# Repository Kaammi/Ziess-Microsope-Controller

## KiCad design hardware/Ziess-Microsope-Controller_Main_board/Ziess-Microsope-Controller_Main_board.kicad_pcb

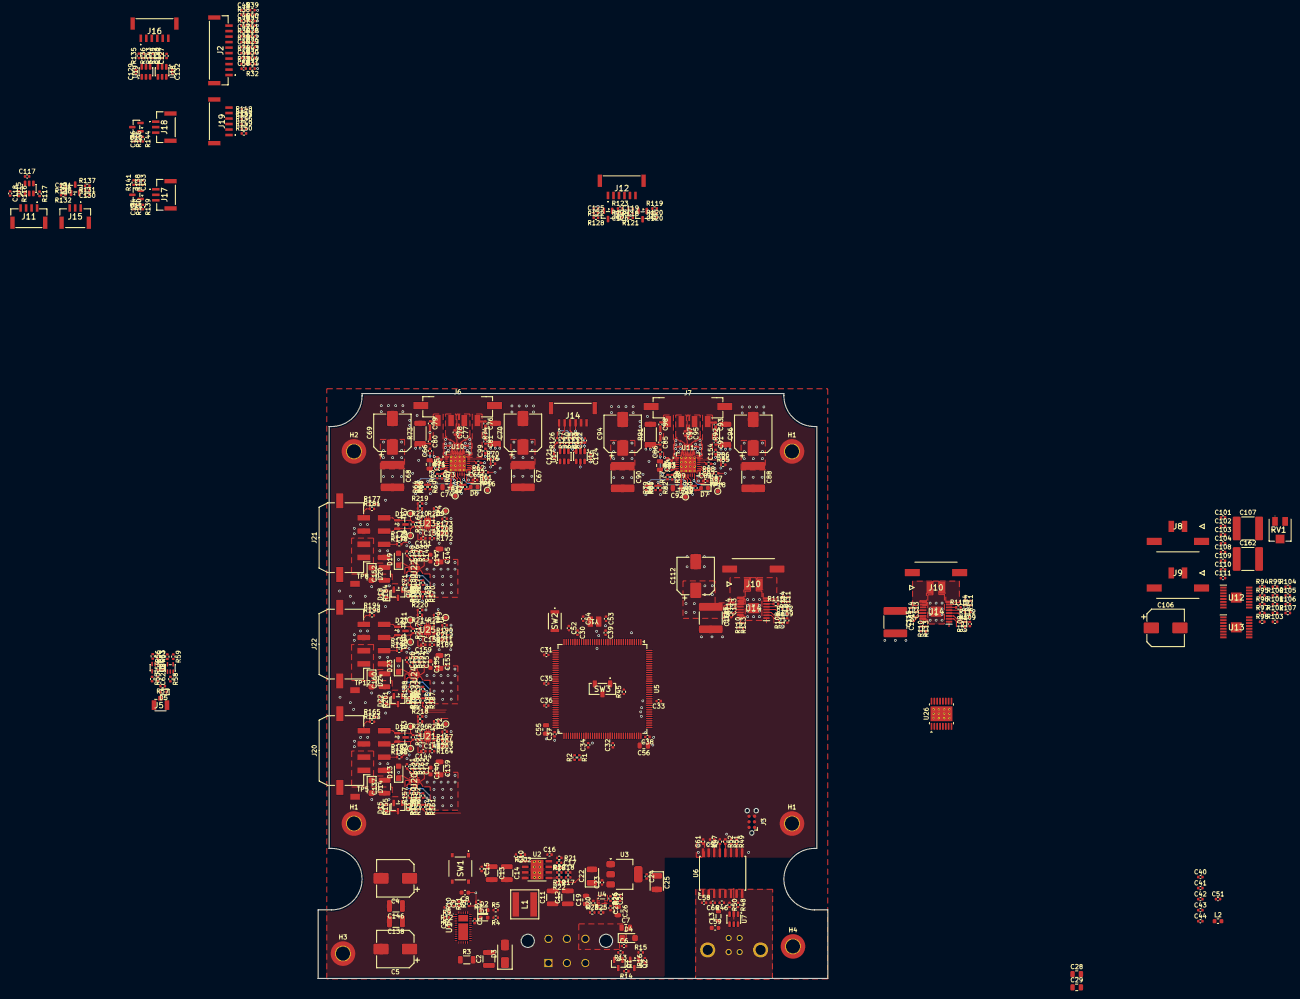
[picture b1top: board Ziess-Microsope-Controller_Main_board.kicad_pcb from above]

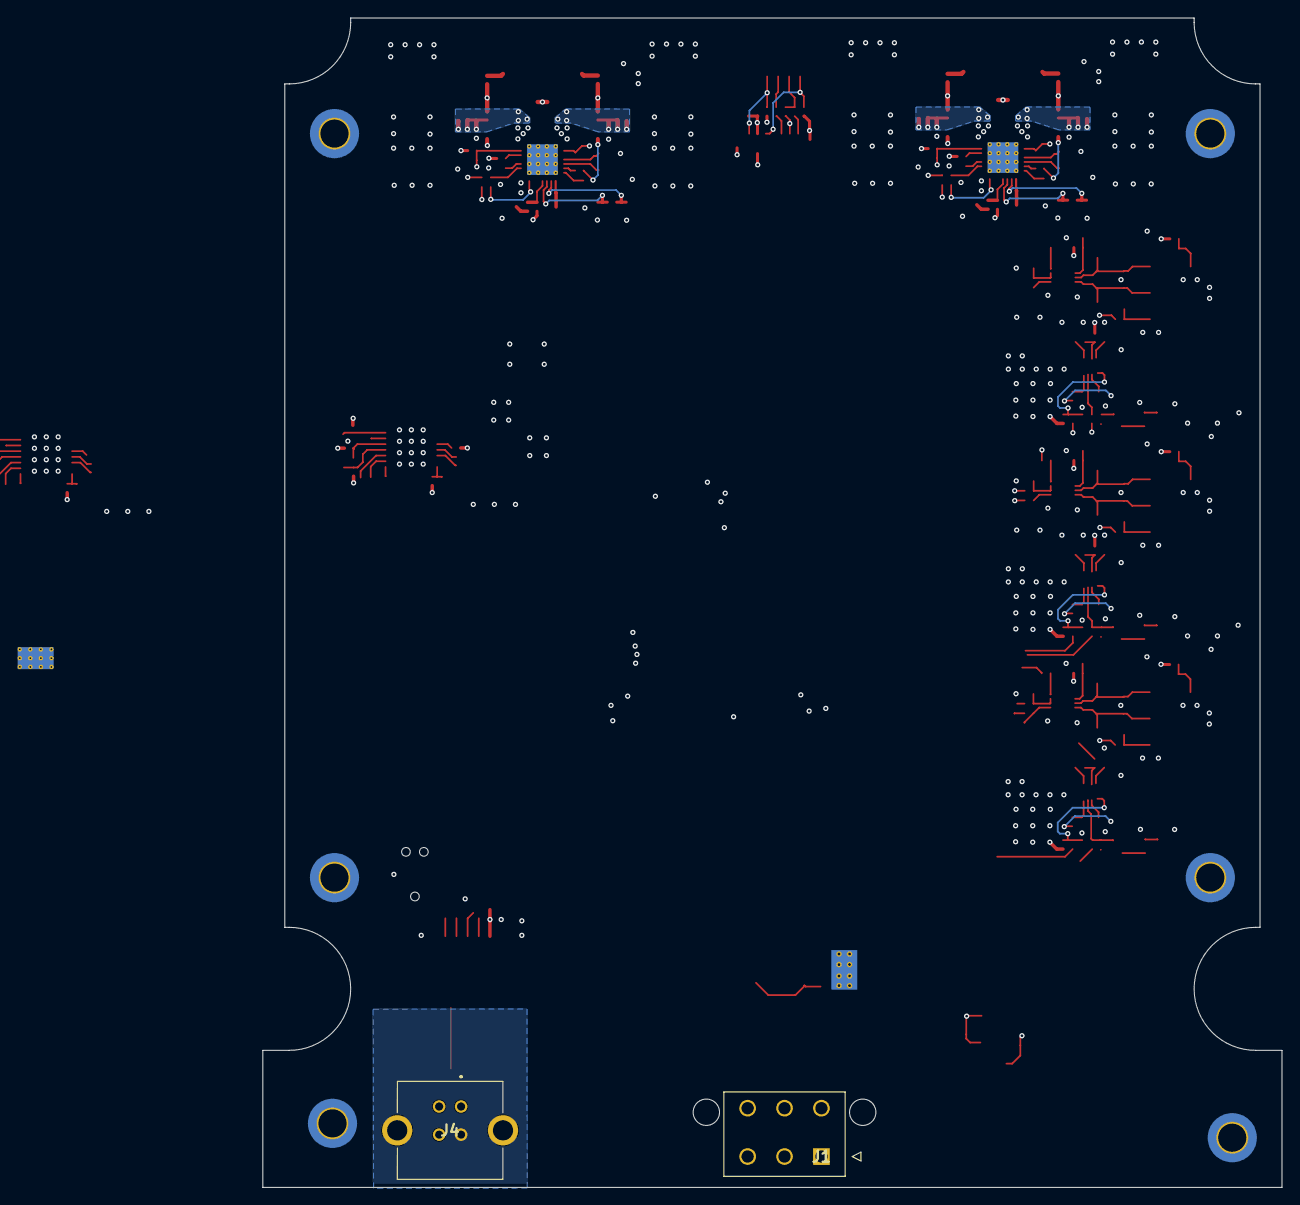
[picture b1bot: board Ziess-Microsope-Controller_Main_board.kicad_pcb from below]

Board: 4 copper layers, 116.0 x 133.1 mm, 498 parts (2 on the bottom side), 244 nets.

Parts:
C1, C3, C6, C9, C10, C20, C21, C23, C24, C27, C30, C31, C32, C33, C34, C35, C36, C37, C38, C39, C40, C42, C43, C44, C45, C46, C47, C48, C49, C50, C51, C52, C57, C58, C60, C61, C65, C66, C71, C72, C73, C80, C81, C82, C83, C85, C86, C87, C89, C91, C99, C101, C102, C104, C108, C109, C111, C113, C113#2, C114, C114#2, C116, C116#2, C117, C118, C119, C120, C121, C123, C124, C125, C126, C128, C129, C130, C131, C132, C133, C134, C135, C136, C143, C144, C150, C151, C154, C158, C159: 100nF; C_0402_1005Metric
C2, C13, C14: 22uF; C_1210_3225Metric
C4, C5, C106, C112: 220uF; CP_Elec_8x10
C7: 10uF; C_0805_2012Metric
C8: 1nF; C_0603_1608Metric
C11, C12: 47uF; C_1210_3225Metric
C15, C62, C63: 100nF; R_0402_1005Metric
C16: 10nF; C_0402_1005Metric
C17: 120pF; C_0402_1005Metric
C18: 12nF; C_0402_1005Metric
C19, C26, C28, C29, C74, C92: 4.7uF; C_0805_2012Metric
C22, C25: 22uF; CP_EIA-3528-21_Kemet-B
C41, C122, C127: 1uF; C_0402_1005Metric
C53, C54: 10pf; C_0402_1005Metric
C55, C56: 2.2uF; C_0805_2012Metric
C59: 2.2uF; C_0603_1608Metric
C67, C68, C88, C90, C107, C161, C161#2, C162: 10uF; C_2220_5750Metric
C69, C70, C94, C96: 100uF; CP_Elec_8x10
C75, C84: 22nF; C_0805_2012Metric
C76, C77, C78, C79, C93, C95, C97, C98: 470pF; C_0402_1005Metric
C103, C110, C115, C115#2, C141, C148, C156: 22nF; C_0402_1005Metric
C137, C152, C160: 10uF; C_1210_3225Metric
C138, C146: 47uf; C_1210_3225Metric
C139, C145, C153: 1uF; C_1206_3216Metric
C140, C147, C155: 100nF; C_0603_1608Metric
C142, C149, C157: 3.3nF; C_0402_1005Metric
D1, D6, D7: RED; LED_0603_1608Metric
D2, D15, D18, D22: GREEN; LED_0603_1608Metric
D3: SMAJ15A; D_SMA
D4: SMF5V0A; D_SMF
D5: TPD1E10B06DYARQ1; D_SOD-523
D8, D9, D10, D11, D12: SP0502BAHT; SOT-23
D13, D19, D23: PMEG4030ER; Nexperia_CFP3_SOD-123W
D14, D20, D24: SMF15A; D_SMF
D16, D17, D21: SM712_SOT23; SOT-23
H1, H1#2, H1#3, H2, H3, H4: MountingHole_Pad; MountingHole_3.2mm_M3_DIN965_Pad_TopBottom
J1: 172447-0006; 172447-YY06
J2: Conn_01x10; BM10BGHSTBT
J3: TC2030; Tag-Connect_TC2030-IDC-NL_2x03_P1.27mm_Vertical
J4: USB_B; UJ2BV1TH
J5: U.FL-R-SMT-1_10; U.FL-R-SMT-1_10_
J6, J7: 43650-0424; Molex_Micro-Fit_3.0_43650-0424_1x04-1MP_P3.00mm_Vertical
J8, J9, J10, J10#2: 43650-0224; 43650-02YY_242526
J11: BM04B-GHS-TBT; BM04BGHSTBTLFSN
J12, J14, J16, J19: BM06B-GHS-TBT; BM06BGHSTBTLFSN
J15, J17, J18: BM03B-GHS-TBT; BM03BGHSTBTLFSN
J20, J21, J22: 43045-0810; Molex_Micro-Fit_3.0_43045-0810_2x04-1MP_P3.00mm_Horizontal
L1: 15uH; SRP6060FA150M
L2: FCM1608KF-601T05; L_0603_1608Metric
L3: BLM21PG221SN1D; L_0805_2012Metric
Q1: BSS84; SOT-23
Q2, Q3, Q4, Q5: 2N7002; SOT-23
R1: 22k; R_0402_1005Metric
R2, R19, R57, R76, R85: 100k; R_0402_1005Metric
R3: 0.002; R_1206_3216Metric
R4, R5, R8, R9, R13, R14, R16, R25, R26, R27, R28, R29, R30, R31, R32, R39, R40, R41, R42, R43, R44, R45, R52, R54, R70, R86, R94, R102, R108, R108#2, R125, R126, R127, R134, R135, R136, R153, R156, R158, R159, R160, R162, R163, R164, R165, R166, R167, R169, R172, R173, R176, R177, R178, R179, R180, R181, R182, R183, R186, R189, R190, R193, R194, R195, R196, R197, R198, R199, R200, R206, R210, R214, R218, R219, R220: 10k; R_0402_1005Metric
R6, R17: 51.1; R_0402_1005Metric
R7: 130k; R_0402_1005Metric
R10: 15k; R_0402_1005Metric
R11: 57.6k; R_0402_1005Metric
R12: 1.78k; R_0402_1005Metric
R15, R46, R47, R53, R56, R59, R63, R64, R65, R67, R68, R69, R71, R77, R78, R79, R80, R81, R82, R89, R96, R97, R99, R100, R103, R104, R105, R106, R110, R110#2, R111, R111#2, R113, R113#2, R114, R114#2, R202: 0; R_0402_1005Metric
R18, R21: R_0402_1005Metric
R20: 3.74k; R_0402_1005Metric
R22, R24: 19.1k; R_0402_1005Metric
R23: 33k; R_0402_1005Metric
R33, R34, R35, R36, R37, R38: 330; R_0402_1005Metric
R48, R49, R50, R51: 24; R_0402_1005Metric
R55: 47; R_0402_1005Metric
R58, R66, R84, R95, R109, R109#2: 1k; R_0402_1005Metric
R61, R62, R87, R88, R129, R130, R142, R143, R148, R149, R150: 22; R_0402_1005Metric
R72, R90: 1K; R_0402_1005Metric
R73, R74, R91, R92: 0.1; R_2010_5025Metric
R75, R83: 20k; R_0402_1005Metric
R98, R112, R112#2: 11k; R_0402_1005Metric
R101, R115, R115#2: 6.8k; R_0402_1005Metric
R107: 1.62k; R_0402_1005Metric
R116, R117: 3.3k; R_0402_1005Metric
R118, R119, R120, R121, R122, R123, R124, R128, R131, R132, R133, R137, R138, R139, R140, R141, R144, R145: 10K; R_0402_1005Metric
R146, R147: 2.2k; R_0402_1005Metric
R151, R170, R187: 470k; R_0402_1005Metric
R152, R175, R192: 82k; R_0402_1005Metric
R154, R168, R185, R203, R204, R205, R207, R208, R209, R211, R212, R213: 100; R_0402_1005Metric
R155, R184, R201: 1.5k; R_0402_1005Metric
R157, R171, R188: 390k; R_0402_1005Metric
R161, R174, R191: 1.65k; R_0402_1005Metric
R215, R216, R217: 120; R_0402_1005Metric
RV1: 10k; 3314J-1
SW1: RESET; PTS526SM15SMTR2LFS
SW2: SW_Push; SKRKAEE010
SW3: CJS1201A
TP1, TP6, TP10: ACC1_A; TestPoint_Pad_D1.0mm
TP2, TP4, TP9: ACC1_DIR; TestPoint_Pad_D1.0mm
TP3, TP7, TP11: ACC1_B; TestPoint_Pad_D1.0mm
TP5, TP8, TP12: ACC1_12V_OUT; HARWIN_S2751-46R
TP16, TP18: X_UART; TestPoint_Pad_D1.0mm
TP17, TP19: 5VOUT; TestPoint_Pad_D1.0mm
U1: TPS24751RUVR
U2: TPS54336ADDA; TI_SO-PowerPAD-8_ThermalVias
U3: AMS1117-3.3; SOT-223-3_TabPin2
U4: TPS2116DRL; SOT-583-8
U5: STM32F765ZGTx; LQFP-144_20x20mm_P0.5mm
U6: ADUM3160; SOIC-16W_7.5x10.3mm_P1.27mm
U7: USBLC6-2SC6; SOT-23-6
U8: 74AHCT1G125; SOT-353_SC-70-5
U9: 74LVC1G17; SOT-353_SC-70-5
U10, U11: TMC2209-LA; VQFN-28-1EP_5x5mm_P0.5mm_EP3.7x3.7mm_ThermalVias
U12, U13, U14, U14#2: DRV8876PWPR; SOP65P640X120-17N
U15, U16, U17, U18, U19: SN74LVC2G17DBV; SOT-23-6
U20, U22, U24: TPS259472LRPWR
U21, U23, U25: THVD2450VDRCR
U26: DRV8833PWP; HTSSOP-16-1EP_4.4x5mm_P0.65mm_EP3.4x5mm_Mask2.46x2.31mm_The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
Y1: Crystal_Small; XTAL_NX3225GD-8MHZ-STD-CRA-3_NDK

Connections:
+3.3V: C24.1, C25.1, C28.2, C29.2, C30.2, C31.2, C32.2, C33.2, C34.2, C35.2, C36.2, C37.2, C38.2, C39.2, C42.2, C43.2, C44.2, C51.2, C57.1, C61.1, C63.1, C65.1, C82.1, C117.2, C121.2, C122.2, C123.2, C124.2, C127.2, C128.2, C129.2, C132.2, C135.2, C143.2, C144.2, C150.2, C151.2, C158.2, C159.2, J2.2, J3.1, J14.6, J16.6, J19.6, L2.2, R27.1, R28.1, R29.1, R30.1, R31.1, R32.1, R47.2, R63.1, R64.1, R65.1, R70.2, R77.1, R79.1, R81.1, R86.2, R94.1, R95.1, R96.1, R97.1, R102.1, R103.1, R104.1, R108.1, R108#2.1, R109.1, R109#2.1, R110.1, R110#2.1, R111.1, R111#2.1, R118.2, R119.2, R122.2, R123.2, R125.1, R126.1, R127.1, R131.2, R132.2, R134.1, R135.1, R136.1, R138.2, R139.2, R144.2, R146.2, R147.2, R155.2, R159.2, R162.2, R163.2, R164.2, R172.2, R179.2, R181.2, R183.2, R184.2, R189.2, R196.2, R198.2, R200.2, R201.2, R206.1, R210.1, R214.1, RV1.1, SW3.3 (C), U3.2 (VO), U5.6 (VBAT), U5.17 (VDD), U5.30 (VDD), U5.39 (VDD), U5.52 (VDD), U5.62 (VDD), U5.72 (VDD), U5.84 (VDD), U5.95 (VDDUSB), U5.108 (VDD), U5.121 (VDDSDMMC), U5.131 (VDD), U5.143 (PDR_ON), U5.144 (VDD), U6.14 (VDD2), U6.16 (VBUS2), U9.5 (VCC), U10.15 (VCC_IO), U11.15 (VCC_IO), U15.5 (V_{CC}), U16.5 (V_{CC}), U17.5 (V_{CC}), U18.5 (V_{CC}), U19.5 (V_{CC}), U21.1 (VIO), U21.10 (VCC), U23.1 (VIO), U23.10 (VCC), U25.1 (VIO), U25.10 (VCC)
+5V: C11.1, C12.1, C19.1, C20.1, C62.1, L1.2, R17.1, R23.1, R54.1, U4.3 (VIN1), U4.5 (MODE), U8.5 (VCC)
+5VSB: C6.1, C7.1, C26.1, C27.1, C118.2, D4.1 (A1), J1.6, J11.4, Q1.2 (S), R13.2, R116.2, R117.2, U4.6 (VIN2)
+12V: C3.1, C4.1, C5.1, C13.1, C14.1, C15.1, C66.1, C67.1, C68.1, C69.1, C70.1, C71.1, C83.1, C86.1, C88.1, C90.1, C94.1, C96.1, C99.1, C101.1, C102.2, C106.1, C107.1, C108.1, C109.2, C112.1, C113.1, C113#2.1, C114.2, C114#2.2, C138.1, C139.2, C140.2, C145.2, C146.1, C147.2, C153.2, C154.1, C155.2, C161.1, C161#2.1, C162.1, J2.1, R2.1, R18.1, R151.2, R170.2, R187.2, U1.6 (OUT_1), U1.7 (OUT_2), U1.8 (OUT_3), U1.9 (OUT_4), U1.10 (OUT_5), U1.11 (OUT_6), U1.12 (OUT_7), U1.13 (OUT_8), U1.19 (OUT_9), U1.20 (OUT_10), U1.21 (OUT_11), U1.22 (OUT_12), U1.23 (OUT_13), U1.24 (OUT_14), U2.2 (VIN), U10.22 (VS), U10.28 (VS), U11.22 (VS), U11.28 (VS), U12.11 (VM), U13.11 (VM), U14.11 (VM), U14#2.11 (VM), U20.5 (IN), U22.5 (IN), U24.5 (IN)
/ACC1/ACC1_+12V: C137.2, D13.1 (K), D14.1 (A1), J20.1, J20.2, R152.1, TP5.1 (1_1), U20.6 (OUT)
/ACC2/ACC1_+12V: C152.2, D19.1 (K), D20.1 (A1), J21.1, J21.2, R175.1, TP8.1 (1_1), U22.6 (OUT)
/ACC3/ACC1_+12V: C160.2, D23.1 (K), D24.1 (A1), J22.1, J22.2, R192.1, TP12.1 (1_1), U24.6 (OUT)
/DC_DRIVERS/F_EN: U14.1 (EN/IN1), U14#2.1 (EN/IN1)
/DC_DRIVERS/F_FAULT: C116.2, C116#2.2, R108.2, R108#2.2, U14.4 (NFAULT), U14#2.4 (NFAULT)
/DC_DRIVERS/F_NSLEEP: U14.3 (NSLEEP), U14#2.3 (NSLEEP)
/DC_DRIVERS/F_PH: U14.2 (PH/IN2), U14#2.2 (PH/IN2)
/DC_DRIVERS/F_SENSE: R115.1, R115#2.1, U14.6 (IPROPI), U14#2.6 (IPROPI)
/DC_DRIVERS/J_FAULT: C104.2, R94.2, U12.4 (NFAULT)
/DC_DRIVERS/J_SENSE: R101.1, U12.6 (IPROPI)
/DC_DRIVERS/Z_FAULT: C111.2, R102.2, U13.4 (NFAULT)
/DC_DRIVERS/Z_SENSE: R107.1, U13.6 (IPROPI)
/LIM_ENC/J_ENC_OUT: R150.2, U5.126 (PG11)
/LIM_ENC/J_ENC_SCL: R146.1, R149.2, U5.125 (PG10)
/LIM_ENC/J_ENC_SDA: R147.1, R148.2, U5.124 (PG9)
/LIM_ENC/XY_ENC_CLK: U17.3 (2A), U19.3 (2A)
/LIM_ENC/X_ENC_CLK_OUTPUT: J14.3, R129.1
/LIM_ENC/X_ENC_CS_OUTPUT: J14.2, R127.2, R130.1
/LIM_ENC/X_ENC_DO_INPUT: J14.4, R125.2, U16.1 (1A)
/LIM_ENC/X_ENC_INDEX_INPUT: J14.1, R126.2, U16.3 (2A)
/LIM_ENC/X_LIM_1: R124.2, U5.36 (PA2)
/LIM_ENC/X_LIM_2: R128.2, U5.37 (PA3)
/LIM_ENC/Y_ENC_CLK_OUTPUT: J16.3, R142.1
/LIM_ENC/Y_ENC_CS_OUTPUT: J16.2, R136.2, R143.1
/LIM_ENC/Y_ENC_DO_INPUT: J16.4, R134.2, U18.1 (1A)
/LIM_ENC/Y_ENC_INDEX_INPUT: J16.1, R135.2, U18.3 (2A)
/LIM_ENC/Y_LIM_1: R120.2, U5.34 (PA0)
/LIM_ENC/Y_LIM_2: R121.2, U5.35 (PA1)
/MCU/12V_SENSE: R1.1, R2.2, U5.80 (PD11)
/MCU/USB_CONNECT: R52.2, U5.102 (PA10), U6.12 (PIN)
/MCU/USB_DN: R51.1, U5.103 (PA11)
/MCU/USB_DP: R49.1, U5.104 (PA12)
/MCU/XY_UART_RX: R66.2, R84.1, TP16.1 (1_1), U10.14 (~PD/UART)
/MCU/XY_UART_TX: R66.1, R84.2, TP18.1 (1_1), U11.14 (~PD/UART)
/MCU/X_EN: R75.1, U10.2 (~EN)
/MCU/X_STDBY: R70.1, R76.1, U10.20 (STDBY)
/MCU/Y_EN: R83.1, U11.2 (~EN)
/MCU/Y_STDBY: R85.1, R86.1, U11.20 (STDBY)
/POWER_INPUT/PWR_EN: J1.3, Q1.3 (D), R14.2
/POWER_INPUT/VIN: C1.1, C2.1, D3.1 (A1), J1.1, J1.2, R3.2, R4.1, R5.1, R6.2, R7.1, U1.29 (VCC)
EXP_GPIO_1: C50.2, R32.2, R33.2, R44.1, U5.115 (PD1)
EXP_GPIO_2: C49.2, R31.2, R34.2, R43.1, U5.114 (PD0)
EXP_GPIO_3: C48.2, R30.2, R35.2, R42.1, U5.113 (PC12)
EXP_GPIO_4: C47.2, R29.2, R36.2, R41.1, U5.112 (PC11)
EXP_GPIO_5: C46.2, R28.2, R37.2, R40.1, U5.111 (PC10)
EXP_GPIO_6: C45.2, R27.2, R38.2, R39.1, U5.110 (PA15)
GND: C1.2, C2.2, C3.2, C4.2, C5.2, C6.2, C7.2, C8.2, C9.2, C11.2, C12.2, C13.2, C14.2, C15.2, C16.2, C17.2, C18.2, C19.2, C20.2, C22.2, C23.2, C24.2, C25.2, C26.2, C27.2, C28.1, C29.1, C30.1, C31.1, C32.1, C33.1, C34.1, C35.1, C36.1, C37.1, C38.1, C39.1, C40.1, C41.1, C42.1, C43.1, C44.1, C45.1, C46.1, C47.1, C48.1, C49.1, C50.1, C51.1, C52.1, C53.1, C54.1, C55.1, C56.1, C57.2, C61.2, C62.2, C63.2, C65.2, C66.2, C67.2, C68.2, C69.2, C70.2, C72.1, C73.1, C74.2, C76.2, C77.2, C78.2, C79.2, C80.1, C81.1, C82.2, C85.1, C86.2, C87.1, C88.2, C89.1, C90.2, C91.1, C92.2, C93.2, C94.2, C95.2, C96.2, C97.2, C98.2, C99.2, C101.2, C104.1, C111.1, C112.2, C113.2, C113#2.2, C116.1, C116#2.1, C117.1, C118.1, C119.1, C120.1, C121.1, C122.1, C123.1, C124.1, C125.1, C126.1, C127.1, C128.1, C129.1, C130.1, C131.1, C132.1, C133.1, C134.1, C135.1, C136.1, C137.1, C138.2, C139.1, C140.1, C141.1, C142.1, C143.1, C144.1, C145.1, C146.2, C147.1, C148.1, C149.1, C150.1, C151.1, C152.1, C153.1, C154.2, C155.1, C156.1, C157.1, C158.1, C159.1, C160.1, C161.2, C161#2.2, C162.2, D3.2 (A2), D4.2 (A2), D5.1 (A1), D6.1 (K), D7.1 (K), D8.3 (A), D9.3 (A), D10.3 (A), D11.3 (A), D12.3 (A), D13.2 (A), D14.2 (A2), D16.3 (common), D17.3 (common), D19.2 (A), D20.2 (A2), D21.3 (common), D23.2 (A), D24.2 (A2), H1.1 (1_1), H1#2.1 (1_1), H1#3.1 (1_1), H2.1 (1_1), H3.1 (1_1), H4.1 (1_1), J1.4, J1.5, J2.3, J2.4, J3.5, J5.1, J5.2 (Ext), J11.1, J12.1, J12.4, J14.5, J15.1, J16.5, J17.1, J18.3, J19.1, J19.5, J20.3, J20.5, J21.3, J21.5, J22.3, J22.5, Q2.2 (S), Q3.2 (S), Q4.2 (S), Q5.2 (S), R1.2, R10.2, R11.2, R12.2, R14.1, R16.1, R21.2, R22.2, R25.2, R39.2, R40.2, R41.2, R42.2, R43.2, R44.2, R52.1, R57.1, R67.2, R68.2, R69.2, R73.2, R74.2, R75.2, R76.2, R78.2, R80.2, R82.2, R83.2, R85.2, R91.2, R92.2, R98.2, R99.2, R100.2, R101.2, R105.2, R106.2, R107.2, R112.2, R112#2.2, R113.2, R113#2.2, R114.2, R114#2.2, R115.2, R115#2.2, R156.1, R157.1, R160.1, R161.1, R167.1, R169.1, R171.1, R173.1, R174.1, R180.1, R186.1, R188.1, R190.1, R191.1, R197.1, R218.2, R219.2, R220.2, RV1.3, SW1.1, SW2.1, SW3.1 (A), U1.4 (GND_1), U1.28 (GND_2), U1.32 (GND_3), U1.36 (GND_4), U1.37 (GND_5), U2.4 (GND), U2.9 (ETPAD), U3.1 (GND), U4.1 (GND), U5.16 (VSS), U5.31 (VSSA), U5.38 (VSS), U5.51 (VSS), U5.61 (VSS), U5.83 (VSS), U5.94 (VSS), U5.107 (VSS), U5.120 (VSS), U5.130 (VSS), U6.9 (GND2), U6.15 (GND2), U8.3 (GND), U9.3 (GND), U10.3 (GND), U10.13 (CLK), U10.18 (GND), U10.25 (NC), U10.29 (GND), U11.3 (GND), U11.13 (CLK), U11.18 (GND), U11.25 (NC), U11.29 (GND), U12.9 (PGND), U12.15 (GND), U12.17 (EP), U13.9 (PGND), U13.15 (GND), U13.17 (EP), U14.9 (PGND), U14.15 (GND), U14.17 (EP), U14#2.9 (PGND), U14#2.15 (GND), U14#2.17 (EP), U15.2 (GND), U16.2 (GND), U17.2 (GND), U18.2 (GND), U19.2 (GND), U20.8 (GND), U21.6 (GND), U21.EP1, U21.EP2, U21.EP3, U21.EP4, U21.EP5, U22.8 (GND), U23.6 (GND), U23.EP1, U23.EP2, U23.EP3, U23.EP4, U23.EP5, U24.8 (GND), U25.6 (GND), U25.EP1, U25.EP2, U25.EP3, U25.EP4, U25.EP5
GNDD: C58.2, C59.1, C60.2, J4.4 (GND), J4.5 (Shield), J4.6 (Shield), U6.2 (GND1), U6.8 (GND1), U7.2 (GND)
MCU_RESET: C52.2, J3.3, SW2.2, U5.25 (NRST)
unnamed: C10.1, R202.2
unnamed: C18.1, R20.2
unnamed: C106.2, C107.2, C108.2
unnamed: D1.2 (A), R4.2
unnamed: D1.1 (K), U1.30 (FLTB)
unnamed: D2.2 (A), R5.2
unnamed: D2.1 (K), U1.31 (PGB)
unnamed: D5.2 (A2), J5.3 (In), R55.2, R57.2, R58.2
unnamed: D6.2 (A), R72.1
unnamed: D7.2 (A), R90.1
unnamed: D15.2 (A), R155.1
unnamed: D15.1 (K), Q3.3 (D)
unnamed: D16.1 (A1), J20.8, R215.1, TP3.1 (1_1), U21.8 (A)
unnamed: D16.2 (A2), J20.7, R215.2, TP1.1 (1_1), U21.9 (B)
unnamed: D17.1 (A1), J21.8, R216.1, TP7.1 (1_1), U23.8 (A)
unnamed: D17.2 (A2), J21.7, R216.2, TP6.1 (1_1), U23.9 (B)
unnamed: D18.2 (A), R184.1
unnamed: D18.1 (K), Q4.3 (D)
unnamed: D21.1 (A1), J22.8, R217.1, TP11.1 (1_1), U25.8 (A)
unnamed: D21.2 (A2), J22.7, R217.2, TP10.1 (1_1), U25.9 (B)
unnamed: D22.2 (A), R201.1
unnamed: D22.1 (K), Q5.3 (D)
unnamed: J2.5, R33.1
unnamed: J2.6, R34.1
unnamed: J2.7, R35.1
unnamed: J2.8, R36.1
unnamed: J2.9, R37.1
unnamed: J2.10, R38.1
unnamed: J4.3 (D+), U7.6 (I/O1)
unnamed: J4.2 (D-), U7.4 (I/O2)
unnamed: C59.2, J4.1 (VBUS), L3.1
unnamed: C79.1, J6.1, U10.1 (OB2)
unnamed: C78.1, J6.2, U10.26 (OB1)
unnamed: C77.1, J6.3, U10.24 (OA1)
unnamed: C76.1, J6.4, U10.21 (OA2)
unnamed: C98.1, J7.1, U11.1 (OB2)
unnamed: C97.1, J7.2, U11.26 (OB1)
unnamed: C95.1, J7.3, U11.24 (OA1)
unnamed: C93.1, J7.4, U11.21 (OA2)
unnamed: J8.1, U12.10 (OUT2)
unnamed: J8.2, U12.8 (OUT1)
unnamed: J9.1, U13.10 (OUT2)
unnamed: J9.2, U13.8 (OUT1)
unnamed: J10.1, J10#2.1, U14.10 (OUT2), U14#2.10 (OUT2)
unnamed: J10.2, J10#2.2, U14.8 (OUT1), U14#2.8 (OUT1)
unnamed: J11.2, R117.1, U15.3 (2A)
unnamed: J11.3, R116.1, U15.1 (1A)
unnamed: C125.2, D9.2 (K), J12.2, R122.1, R128.1
unnamed: C126.2, D9.1 (K), J12.3, R123.1, R124.1
unnamed: C119.2, D8.2 (K), J12.5, R118.1, R121.1
unnamed: C120.2, D8.1 (K), J12.6, R119.1, R120.1
unnamed: C130.2, D10.2 (K), J15.2, R131.1, R137.1
unnamed: C131.2, D10.1 (K), J15.3, R132.1, R133.1
unnamed: C133.2, D11.2 (K), J17.2, R138.1, R141.1
unnamed: C134.2, D11.1 (K), J17.3, R139.1, R140.1
unnamed: C136.2, D12.1 (K), J18.1, R144.1, R145.1
unnamed: J19.2, R150.1
unnamed: J19.3, R149.1
unnamed: J19.4, R148.1
unnamed: J20.4, R163.1, R165.1
unnamed: J20.6, R162.1, R166.1
unnamed: J21.4, R177.1, R181.1
unnamed: J21.6, R178.1, R179.1
unnamed: J22.4, R194.1, R198.1
unnamed: J22.6, R195.1, R196.1
unnamed: Q1.1 (G), Q2.3 (D), R13.1
unnamed: Q2.1 (G), R15.1, R16.2
unnamed: Q3.1 (G), R153.1, R159.1, U20.3 (PG/_AUXOFF)
unnamed: Q4.1 (G), R182.1, R183.1, U22.3 (PG/_AUXOFF)
unnamed: Q5.1 (G), R199.1, R200.1, U24.3 (PG/_AUXOFF)
unnamed: R17.2, R19.1
unnamed: R48.2, U7.1 (I/O1)
unnamed: R50.2, U7.3 (I/O2)
unnamed: R53.2, R54.2, U8.1
unnamed: R55.1, U8.4
unnamed: R56.2, U8.2
unnamed: R58.1, U9.2
unnamed: R59.2, U9.4
unnamed: R45.1, SW3.2 (B)
unnamed: R3.1, U1.14 (DRAIN_2), U1.15 (DRAIN_3), U1.16 (DRAIN_4), U1.17 (DRAIN_5), U1.18 (DRAIN_6), U1.26 (SENSE), U1.38 (DRAIN_8)
unnamed: C8.1, R7.2, R8.1, SW1.2, U1.33 (EN)
unnamed: R9.1, R12.1, U1.2 (IMON)
unnamed: R8.2, R10.1, U1.1 (OV)
unnamed: R11.1, U1.34 (PROG)
unnamed: R6.1, U1.3 (SET)
unnamed: C9.1, U1.35 (TIMER)
unnamed: R202.1, U2.1 (BOOT)
unnamed: C17.1, R20.1, U2.6 (COMP)
unnamed: R18.2, R21.1, U2.7 (EN)
unnamed: C10.2, L1.1, U2.3 (PH)
unnamed: C16.1, U2.8 (SS)
unnamed: R19.2, R22.1, U2.5 (VSENSE)
unnamed: C21.1, C22.1, C23.1, R24.1, U3.3 (VI), U4.2 (VOUT), U4.7 (VOUT)
unnamed: R23.2, R25.1, U4.4 (PR1)
unnamed: C21.2, R24.2, R26.1, U4.8 (ST)
unnamed: R45.2, U5.138 (BOOT0)
unnamed: C53.2, U5.23 (PH0), Y1.1
unnamed: C54.2, U5.24 (PH1), Y1.2
unnamed: C55.2, U5.71 (VCAP_1)
unnamed: C56.2, U5.106 (VCAP_2)
unnamed: R49.2, U6.10 (DD+)
unnamed: R51.2, U6.11 (DD-)
unnamed: C60.1, R46.2, U6.3 (VDD1), U6.4 (PDEN)
unnamed: R47.1, U6.13 (SPD)
unnamed: R46.1, U6.5 (SPU)
unnamed: R48.1, U6.7 (UD+)
unnamed: R50.1, U6.6 (UD-)
unnamed: C58.1, L3.2, U6.1 (VBUS1), U7.5 (VBUS)
unnamed: C73.2, C74.1, TP17.1 (1_1), U10.8 (5VOUT)
unnamed: C81.2, R74.1, U10.23 (BRA)
unnamed: C80.2, R73.1, U10.27 (BRB)
unnamed: C75.2, U10.5 (CPI)
unnamed: C75.1, U10.4 (CPO)
unnamed: R71.2, R72.2, U10.11 (DIAG)
unnamed: R62.2, U10.19 (DIR)
unnamed: R64.2, R68.1, U10.9 (MS1/AD0)
unnamed: R65.2, R69.1, U10.10 (MS2/AD1)
unnamed: R63.2, R67.1, U10.7 (SPREAD)
unnamed: R61.2, U10.16 (STEP)
unnamed: C71.2, U10.6 (VCP)
unnamed: C72.2, U10.17 (VREF)
unnamed: C89.2, C92.1, TP19.1 (1_1), U11.8 (5VOUT)
unnamed: C91.2, R92.1, U11.23 (BRA)
unnamed: C85.2, R91.1, U11.27 (BRB)
unnamed: C84.2, U11.5 (CPI)
unnamed: C84.1, U11.4 (CPO)
unnamed: R89.2, R90.2, U11.11 (DIAG)
unnamed: R88.2, U11.19 (DIR)
unnamed: R79.2, R80.1, U11.9 (MS1/AD0)
unnamed: R81.2, R82.1, U11.10 (MS2/AD1)
unnamed: R77.2, R78.1, U11.7 (SPREAD)
unnamed: R87.2, U11.16 (STEP)
unnamed: C83.2, U11.6 (VCP)
unnamed: C87.2, U11.17 (VREF)
unnamed: C103.2, U12.13 (CPH)
unnamed: C103.1, U12.14 (CPL)
unnamed: R97.2, R100.1, U12.7 (IMODE)
unnamed: R96.2, R99.1, U12.16 (PMODE)
unnamed: C102.1, U12.12 (VCP)
unnamed: R95.2, R98.1, U12.5 (VREF)
unnamed: C110.2, U13.13 (CPH)
unnamed: C110.1, U13.14 (CPL)
unnamed: R104.2, R106.1, U13.7 (IMODE)
unnamed: R103.2, R105.1, U13.16 (PMODE)
unnamed: C109.1, U13.12 (VCP)
unnamed: RV1.2, U13.5 (VREF)
unnamed: C115.2, C115#2.2, U14.13 (CPH), U14#2.13 (CPH)
unnamed: C115.1, C115#2.1, U14.14 (CPL), U14#2.14 (CPL)
unnamed: R111.2, R111#2.2, R114.1, R114#2.1, U14.7 (IMODE), U14#2.7 (IMODE)
unnamed: R110.2, R110#2.2, R113.1, R113#2.1, U14.16 (PMODE), U14#2.16 (PMODE)
unnamed: C114.1, C114#2.1, U14.12 (VCP), U14#2.12 (VCP)
unnamed: R109.2, R109#2.2, R112.1, R112#2.1, U14.5 (VREF), U14#2.5 (VREF)
unnamed: R130.2, U17.6 (1Y)
unnamed: R129.2, U17.4 (2Y)
unnamed: R143.2, U19.6 (1Y)
unnamed: R142.2, U19.4 (2Y)
unnamed: C142.2, U20.7 (DVDT_1), U20.13 (DVDT_2)
unnamed: R151.1, R154.1, R156.2, U20.1 (EN/UVLO_1), U20.11 (EN/UVLO_2)
unnamed: R158.2, R161.2, U20.9 (ILM)
unnamed: C141.2, U20.10 (ITIMER_1), U20.14 (ITIMER_2)
unnamed: R157.2, U20.2 (OVLO/_OVCSEL)
unnamed: R152.2, R160.2, U20.4 (PGTH/_~FLT_1), U20.12 (PGTH/_~FLT_2)
unnamed: R205.2, U21.5 (D)
unnamed: R167.2, R204.2, TP2.1 (1_1), U21.3 (DE), U21.4 (~RE)
unnamed: R164.1, R203.2, U21.2 (R)
unnamed: R206.2, R218.1, U21.7 (SLR)
unnamed: C149.2, U22.7 (DVDT_1), U22.13 (DVDT_2)
unnamed: R168.1, R169.2, R170.1, U22.1 (EN/UVLO_1), U22.11 (EN/UVLO_2)
unnamed: R174.2, R176.2, U22.9 (ILM)
unnamed: C148.2, U22.10 (ITIMER_1), U22.14 (ITIMER_2)
unnamed: R171.2, U22.2 (OVLO/_OVCSEL)
unnamed: R175.2, R180.2, U22.4 (PGTH/_~FLT_1), U22.12 (PGTH/_~FLT_2)
unnamed: R209.2, U23.5 (D)
unnamed: R173.2, R208.2, TP4.1 (1_1), U23.3 (DE), U23.4 (~RE)
unnamed: R172.1, R207.2, U23.2 (R)
unnamed: R210.2, R219.1, U23.7 (SLR)
unnamed: C157.2, U24.7 (DVDT_1), U24.13 (DVDT_2)
unnamed: R185.1, R186.2, R187.1, U24.1 (EN/UVLO_1), U24.11 (EN/UVLO_2)
unnamed: R191.2, R193.2, U24.9 (ILM)
unnamed: C156.2, U24.10 (ITIMER_1), U24.14 (ITIMER_2)
unnamed: R188.2, U24.2 (OVLO/_OVCSEL)
unnamed: R192.2, R197.2, U24.4 (PGTH/_~FLT_1), U24.12 (PGTH/_~FLT_2)
unnamed: R213.2, U25.5 (D)
unnamed: R190.2, R212.2, TP9.1 (1_1), U25.3 (DE), U25.4 (~RE)
unnamed: R189.1, R211.2, U25.2 (R)
unnamed: R214.2, R220.1, U25.7 (SLR)
unnamed: U26.13 (GND), U26.17 (GND)
SWCLK: J3.4, U5.109 (PA14)
SWDIO: J3.2, U5.105 (PA13)
SWO: J3.6, U5.133 (PB3)
VDDA: C40.2, C41.2, L2.1, U5.32 (VREF+), U5.33 (VDDA)

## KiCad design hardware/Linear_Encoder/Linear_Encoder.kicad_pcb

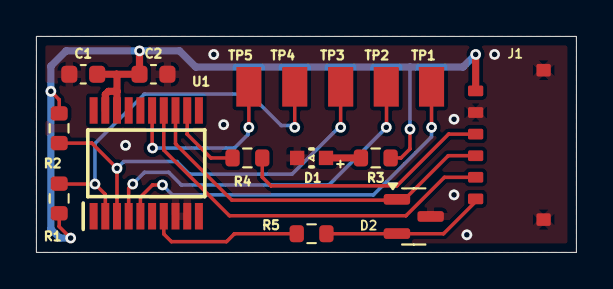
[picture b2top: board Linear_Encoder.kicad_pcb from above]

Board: 2 copper layers, 30.0 x 12.0 mm, 16 parts (0 on the bottom side), 14 nets.

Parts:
C1: 100n; C_0603_1608Metric
C2: 2.2u; C_0603_1608Metric
D1: GREEN; WL-SMCW_0603
D2: SP0502BAHTG; SOT-23
J1: Conn_01x06_Pin; 781715006
R1, R2: 10k; R_0603_1608Metric
R3: 680; R_0603_1608Metric
R4, R5: 0; R_0603_1608Metric
TP1, TP2, TP3, TP4, TP5: TestPoint; HARWIN_S2751-46R
U1: AS5311-ATST-500; SOP65P640X120-20N

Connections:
+3V3: C1.1, C2.1, J1.6, R1.1, R2.1, R3.1, U1.18 (VDD3V3), U1.19 (VDD5V)
/A: TP2.1, U1.4 (A)
/B: TP1.1, U1.5 (B)
/CLK: D2.1 (K1), J1.3, U1.13 (CLK)
/CSN: J1.2, U1.14 (CSN)
/DO: R4.2, U1.12 (DO)
/DO_IN: J1.4, R4.1
/INDEX: R5.2, U1.7 (INDEX)
/INDEX_IN: D2.2 (K2), J1.1, R5.1
/LED: D1.2 (A), R3.2
/MAGDEC: R2.2, TP3.1, U1.3 (MAGDECN)
/MAGIN: R1.2, TP4.1, U1.2 (MAGINCN)
/PWM: TP5.1, U1.15 (PWM)
GND: C1.2, C2.2, D1.1 (K), D2.3 (A), J1.5, U1.8 (VSS), U1.9 (PROG)

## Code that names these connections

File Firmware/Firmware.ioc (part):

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Mcu.Name=STM32F446V(C-E)Tx
Mcu.Package=LQFP100
Mcu.UserName=STM32F446VETx
PA11.Mode=Device_Only
PA11.Signal=USB_OTG_FS_DM
PA12.Mode=Device_Only
PA12.Signal=USB_OTG_FS_DP
PA13.Mode=Trace_Asynchronous_SW
PA13.Signal=SYS_JTMS-SWDIO
PA14.Mode=Trace_Asynchronous_SW
PA14.Signal=SYS_JTCK-SWCLK
PA9.Mode=Activate_VBUS
PA9.Signal=USB_OTG_FS_VBUS
PB3.Mode=Trace_Asynchronous_SW
PB3.Signal=SYS_JTDO-SWO
PH0-OSC_IN.Mode=HSE-External-Oscillator
PH0-OSC_IN.Signal=RCC_OSC_IN
PH1-OSC_OUT.Mode=HSE-External-Oscillator
PH1-OSC_OUT.Signal=RCC_OSC_OUT
RCC.HSE_VALUE=16000000
board=custom
